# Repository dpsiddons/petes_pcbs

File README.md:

# petes_pcbs
various PCB designs

THis is a collection of small PCB designs (in KiCad) that I have done, some for my research adn some for my hobbies. This is just a place to keep them where they are accessible to myself and my colleagues.

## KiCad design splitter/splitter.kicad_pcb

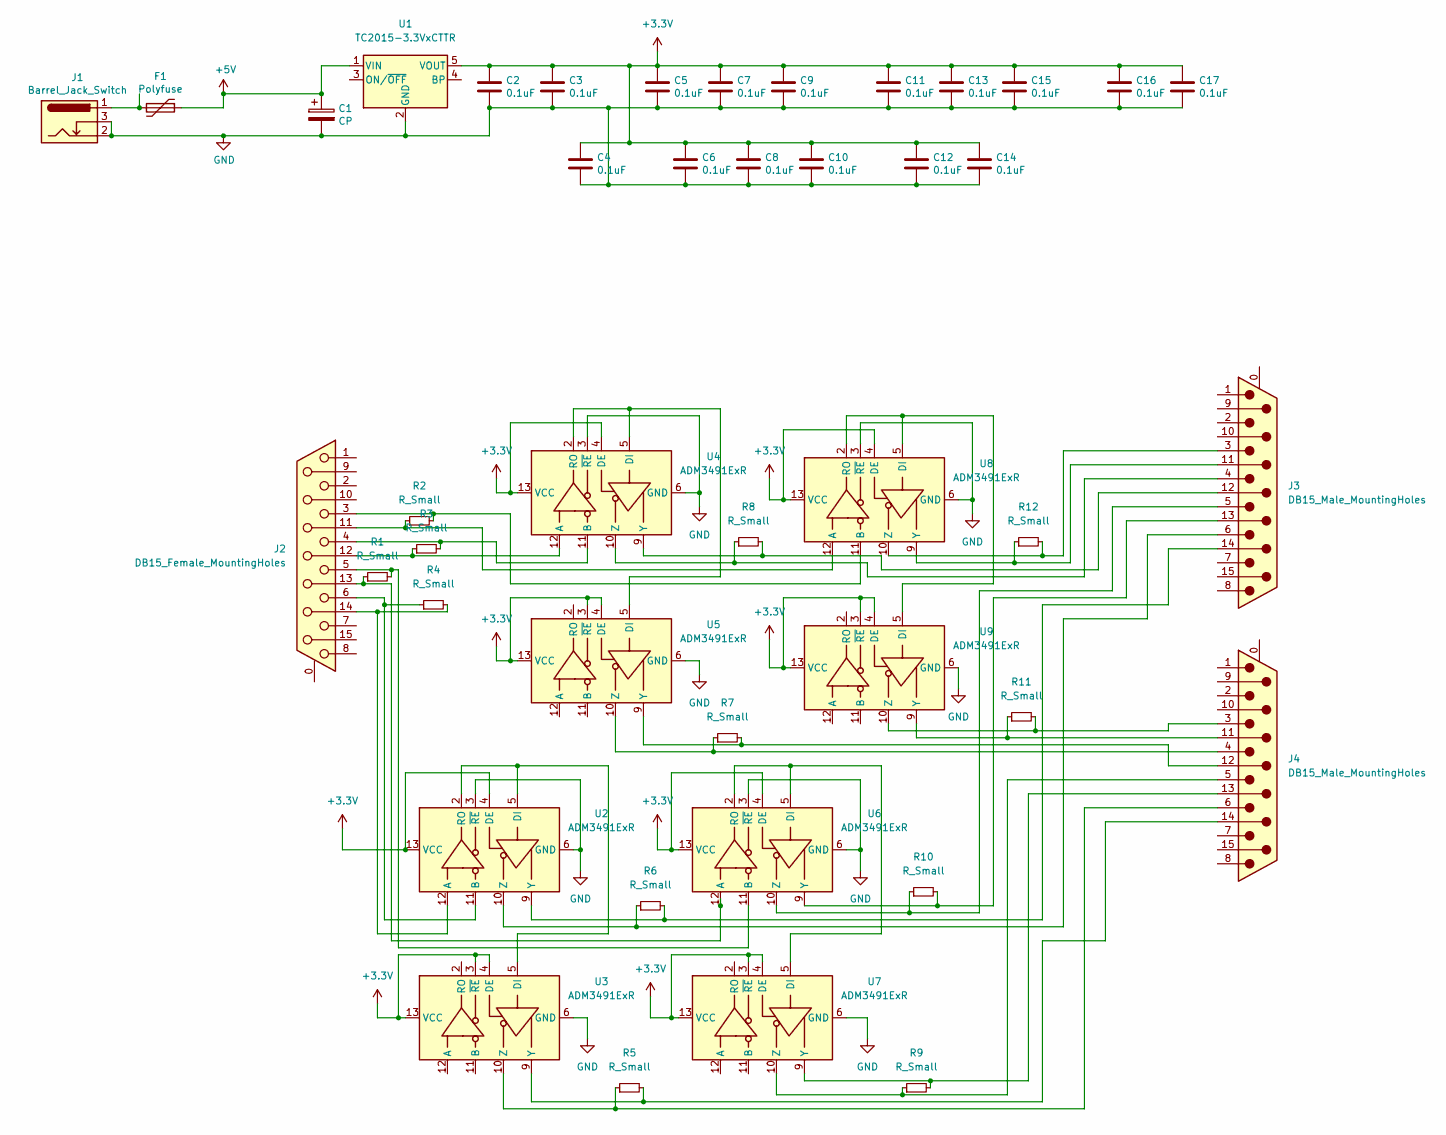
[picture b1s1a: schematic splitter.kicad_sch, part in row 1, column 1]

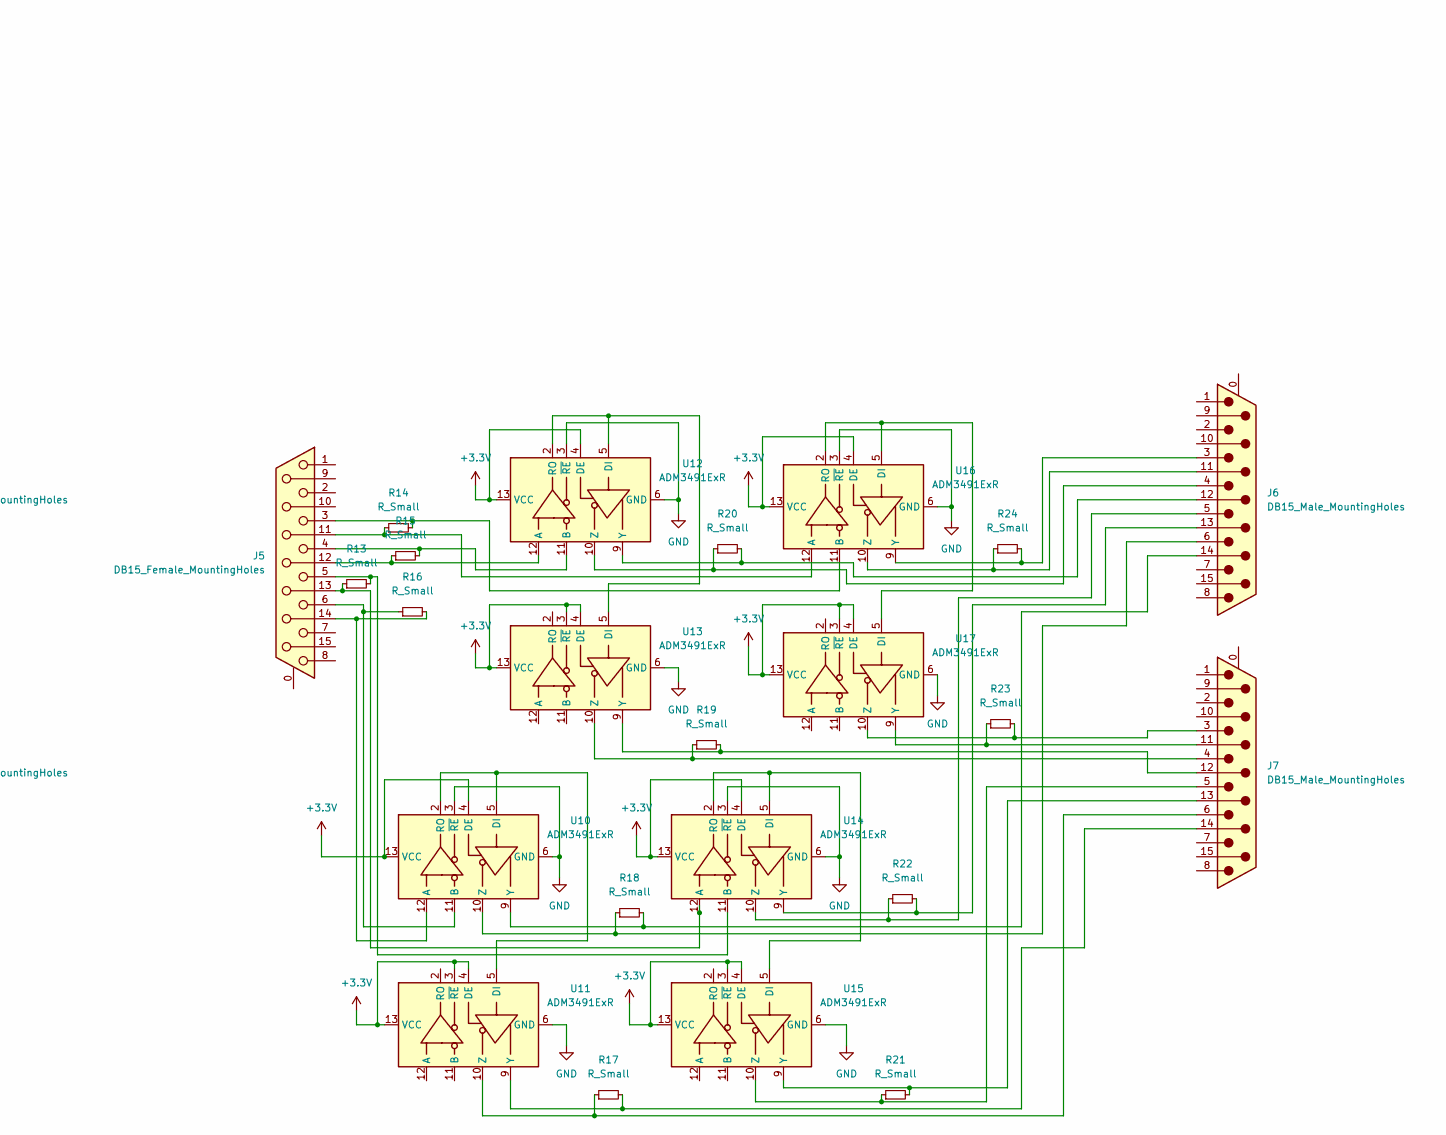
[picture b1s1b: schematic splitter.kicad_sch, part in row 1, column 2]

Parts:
C1: CP; CP_Elec_5x3
C2, C3, C4, C5, C6, C7, C8, C9, C10, C11, C12, C13, C14, C15, C16, C17: 0.1uF; C_0805_2012Metric
F1: Polyfuse; Fuse_2920_7451Metric
J1: Barrel_Jack_Switch; BarrelJack_GCT_DCJ200-10-A_Horizontal
J2, J5: DB15_Female_MountingHoles; DSUB-15_Female_Horizontal_P2.77x2.84mm_EdgePinOffset4.94mm_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
J3, J4, J6, J7: DB15_Male_MountingHoles; DSUB-15_Male_Horizontal_P2.77x2.84mm_EdgePinOffset4.94mm_Ho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
R1, R2, R3, R4, R5, R6, R7, R8, R9, R10, R11, R12, R13, R14, R15, R16, R17, R18, R19, R20, R21, R22, R23, R24: R_Small; R_0402_1005Metric_Pad0.72x0.64mm_HandSolder
U1: TC2015-3.3VxCTTR; SOT-23-5
U2, U3, U4, U5, U6, U7, U8, U9, U10, U11, U12, U13, U14, U15, U16, U17: ADM3491ExR; SOIC-14_3.9x8.7mm_P1.27mm

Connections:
+3V3: C2.1, C3.1, C4.1, C5.1, C6.1, C7.1, C8.1, C9.1, C10.1, C11.1, C12.1, C13.1, C14.1, C15.1, C16.1, C17.1, U1.5 (VOUT), U2.4 (DE), U2.13 (VCC), U2.14 (VCC), U3.3 (~RE), U3.4 (DE), U3.13 (VCC), U3.14 (VCC), U4.4 (DE), U4.13 (VCC), U4.14 (VCC), U5.3 (~RE), U5.4 (DE), U5.13 (VCC), U5.14 (VCC), U6.4 (DE), U6.13 (VCC), U6.14 (VCC), U7.3 (~RE), U7.4 (DE), U7.13 (VCC), U7.14 (VCC), U8.4 (DE), U8.13 (VCC), U8.14 (VCC), U9.3 (~RE), U9.4 (DE), U9.13 (VCC), U9.14 (VCC), U10.4 (DE), U10.13 (VCC), U10.14 (VCC), U11.3 (~RE), U11.4 (DE), U11.13 (VCC), U11.14 (VCC), U12.4 (DE), U12.13 (VCC), U12.14 (VCC), U13.3 (~RE), U13.4 (DE), U13.13 (VCC), U13.14 (VCC), U14.4 (DE), U14.13 (VCC), U14.14 (VCC), U15.3 (~RE), U15.4 (DE), U15.13 (VCC), U15.14 (VCC), U16.4 (DE), U16.13 (VCC), U16.14 (VCC), U17.3 (~RE), U17.4 (DE), U17.13 (VCC), U17.14 (VCC)
+5V: C1.1, F1.1, U1.1 (VIN)
GND: C1.2, C2.2, C3.2, C4.2, C5.2, C6.2, C7.2, C8.2, C9.2, C10.2, C11.2, C12.2, C13.2, C14.2, C15.2, C16.2, C17.2, J1.2, J1.3, U1.2 (GND), U2.3 (~RE), U2.6 (GND), U2.7 (GND), U3.6 (GND), U3.7 (GND), U4.3 (~RE), U4.6 (GND), U4.7 (GND), U5.6 (GND), U5.7 (GND), U6.3 (~RE), U6.6 (GND), U6.7 (GND), U7.6 (GND), U7.7 (GND), U8.3 (~RE), U8.6 (GND), U8.7 (GND), U9.6 (GND), U9.7 (GND), U10.3 (~RE), U10.6 (GND), U10.7 (GND), U11.6 (GND), U11.7 (GND), U12.3 (~RE), U12.6 (GND), U12.7 (GND), U13.6 (GND), U13.7 (GND), U14.3 (~RE), U14.6 (GND), U14.7 (GND), U15.6 (GND), U15.7 (GND), U16.3 (~RE), U16.6 (GND), U16.7 (GND), U17.6 (GND), U17.7 (GND)
unnamed: F1.2, J1.1
unnamed: J2.3, R2.2, U8.11 (B)
unnamed: J2.4, R3.2, U4.11 (B)
unnamed: J2.5, R1.2, U6.11 (B)
unnamed: J2.6, R4.1, U2.11 (B)
unnamed: J2.11 (P111), R2.1, U8.12 (A)
unnamed: J2.12, R3.1, U4.12 (A)
unnamed: J2.13, R1.1, U6.12 (A)
unnamed: J2.14, R4.2, U2.12 (A)
unnamed: J3.3, R12.2, U8.10 (Z)
unnamed: J3.4, R8.1, U4.10 (Z)
unnamed: J3.5, R10.1, U6.10 (Z)
unnamed: J3.6, R6.1, U2.10 (Z)
unnamed: J3.11 (P111), R12.1, U8.9 (Y)
unnamed: J3.12, R8.2, U4.9 (Y)
unnamed: J3.13, R10.2, U6.9 (Y)
unnamed: J3.14, R6.2, U2.9 (Y)
unnamed: J4.3, R11.2, U9.10 (Z)
unnamed: J4.4, R7.1, U5.10 (Z)
unnamed: J4.5, R9.1, U7.10 (Z)
unnamed: J4.6, R5.1, U3.10 (Z)
unnamed: J4.11 (P111), R11.1, U9.9 (Y)
unnamed: J4.12, R7.2, U5.9 (Y)
unnamed: J4.13, R9.2, U7.9 (Y)
unnamed: J4.14, R5.2, U3.9 (Y)
unnamed: J5.3, R14.2, U16.11 (B)
unnamed: J5.4, R15.2, U12.11 (B)
unnamed: J5.5, R13.2, U14.11 (B)
unnamed: J5.6, R16.1, U10.11 (B)
unnamed: J5.11 (P111), R14.1, U16.12 (A)
unnamed: J5.12, R15.1, U12.12 (A)
unnamed: J5.13, R13.1, U14.12 (A)
unnamed: J5.14, R16.2, U10.12 (A)
unnamed: J6.3, R24.2, U16.9 (Y)
unnamed: J6.4, R20.1, U12.10 (Z)
unnamed: J6.5, R22.1, U14.10 (Z)
unnamed: J6.6, R18.1, U10.10 (Z)
unnamed: J6.12, R20.2, U12.9 (Y)
unnamed: J6.13, R22.2, U14.9 (Y)
unnamed: J6.14, R18.2, U10.9 (Y)
unnamed: J7.3, R23.2, U17.10 (Z)
unnamed: J7.4, R19.1, U13.10 (Z)
unnamed: J7.5, R21.1, U15.10 (Z)
unnamed: J7.6, R17.1, U11.10 (Z)
unnamed: J7.11 (P111), R23.1, U17.9 (Y)
unnamed: J7.12, R19.2, U13.9 (Y)
unnamed: J7.13, R21.2, U15.9 (Y)
unnamed: J7.14, R17.2, U11.9 (Y)
unnamed: U2.2 (RO), U2.5 (DI), U3.5 (DI)
unnamed: U4.2 (RO), U4.5 (DI), U5.5 (DI)
unnamed: U6.2 (RO), U6.5 (DI), U7.5 (DI)
unnamed: U8.2 (RO), U8.5 (DI), U9.5 (DI)
unnamed: U10.2 (RO), U10.5 (DI), U11.5 (DI)
unnamed: U12.2 (RO), U12.5 (DI), U13.5 (DI)
unnamed: U14.2 (RO), U14.5 (DI), U15.5 (DI)
unnamed: U16.2 (RO), U16.5 (DI), U17.5 (DI)
unnamed: J6.11 (P111), R24.1, U16.10 (Z)

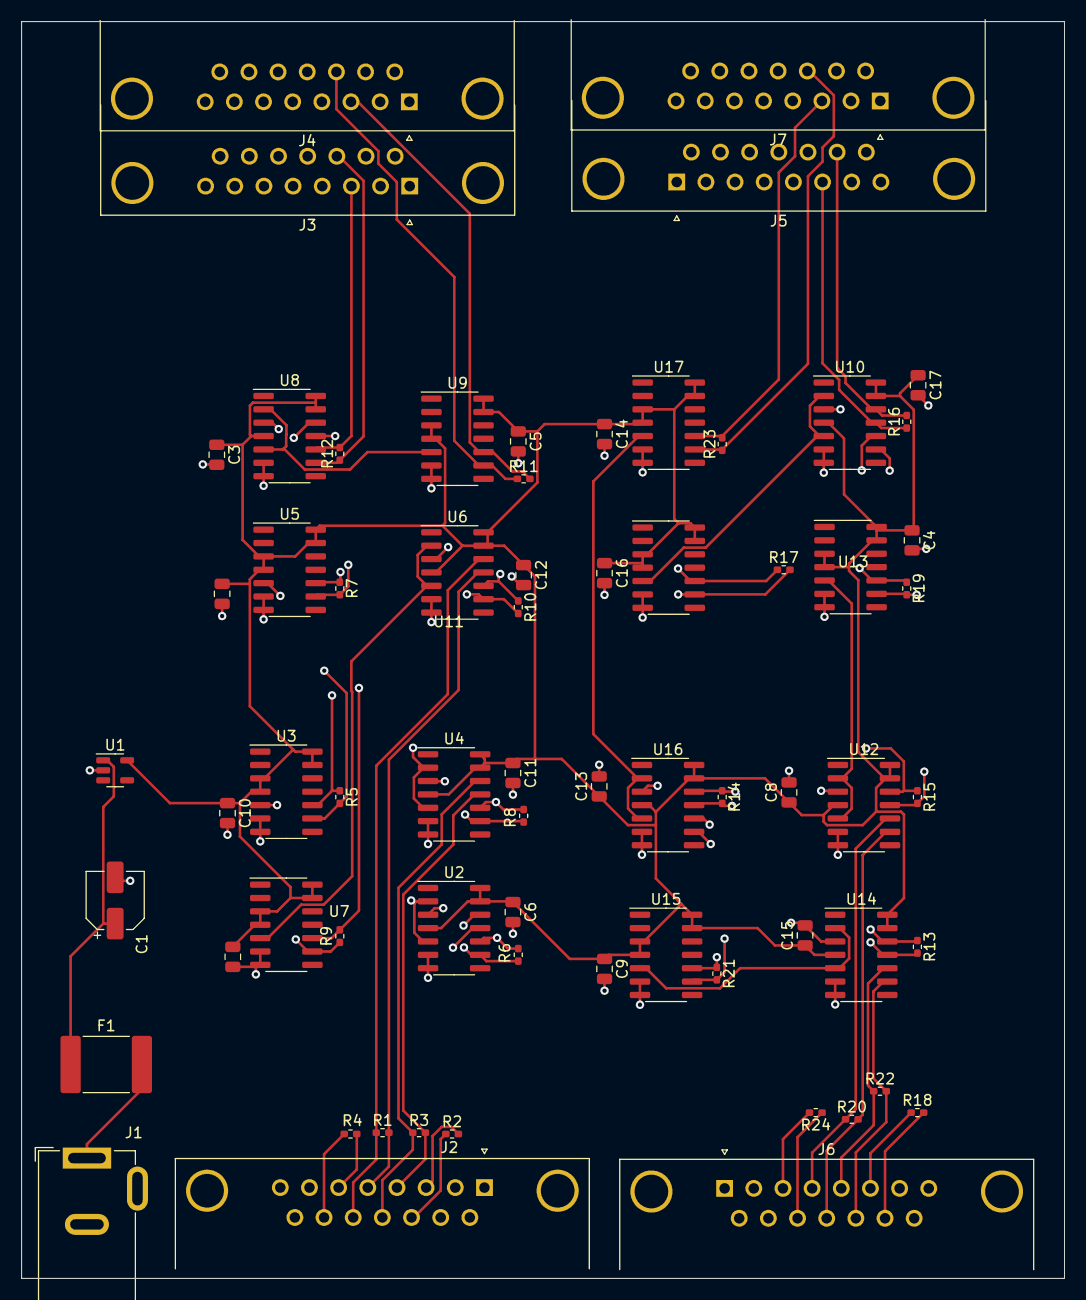
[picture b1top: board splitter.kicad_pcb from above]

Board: 4 copper layers, 99.1 x 119.4 mm, 66 parts (0 on the bottom side), 60 nets.

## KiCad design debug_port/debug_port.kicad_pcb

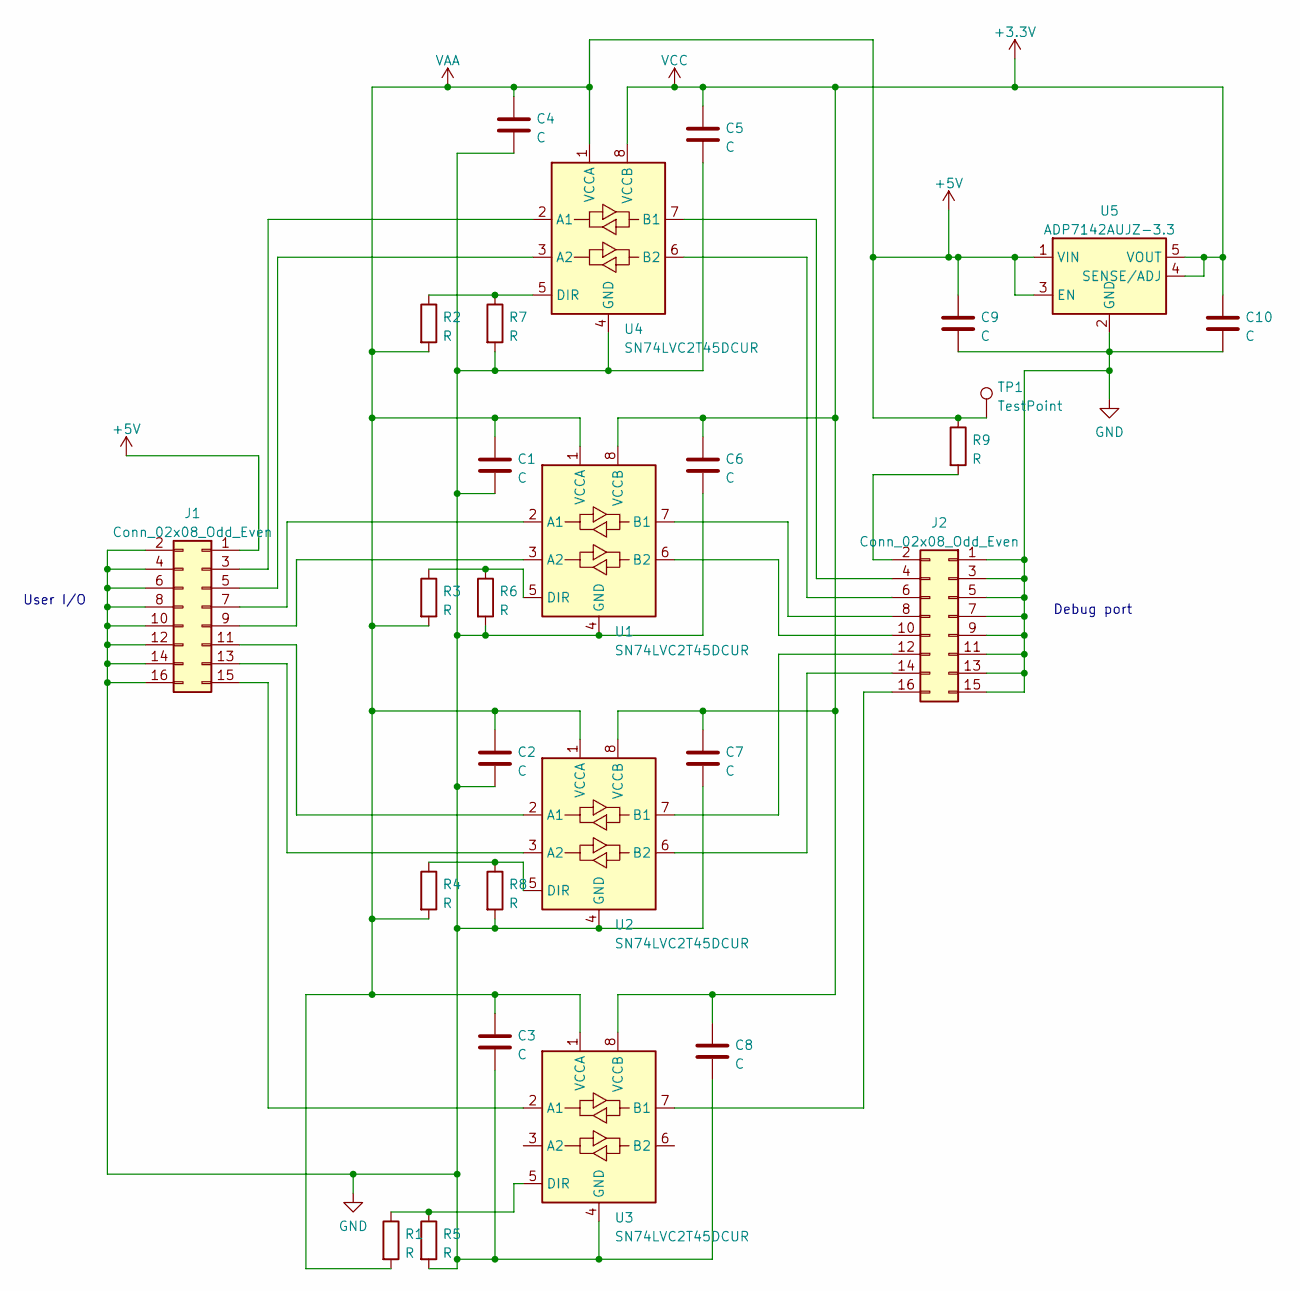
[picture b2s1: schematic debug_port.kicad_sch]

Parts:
C1, C2, C3, C4, C5, C6, C7, C8, C9, C10: C; C_0603_1608Metric_Pad1.08x0.95mm_HandSolder
J1: Conn_02x08_Odd_Even; PinHeader_2x08_P2.54mm_Vertical
J2: Conn_02x08_Odd_Even; PinSocket_2x08_P2.54mm_Horizontal
R1, R2, R3, R4, R5, R6, R7, R8, R9: R; R_0402_1005Metric_Pad0.72x0.64mm_HandSolder
TP1: TestPoint; TestPoint_Pad_1.0x1.0mm
U1, U2, U3, U4: SN74LVC2T45DCUR; VSSOP-8_2.4x2.1mm_P0.5mm
U5: ADP7142AUJZ-3.3; TSOT-23-5

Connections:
+3.3V: C5.1, C6.1, C7.1, C8.1, C10.1, U1.8 (VCCB), U2.8 (VCCB), U3.8 (VCCB), U4.8 (VCCB), U5.4 (SENSE/ADJ), U5.5 (VOUT)
+5V: C1.1, C2.1, C3.1, C4.1, C9.1, J1.1, R1.2, R2.2, R3.2, R4.2, R9.1, TP1.1, U1.1 (VCCA), U2.1 (VCCA), U3.1 (VCCA), U4.1 (VCCA), U5.1 (VIN), U5.3 (EN)
GND: C1.2, C2.2, C3.2, C4.2, C5.2, C6.2, C7.2, C8.2, C9.2, C10.2, J1.2, J1.4, J1.6, J1.8, J1.10, J1.12, J1.14, J1.16, J2.1, J2.3, J2.5, J2.7, J2.9, J2.11, J2.13, J2.15, R5.2, R6.2, R7.2, R8.2, U1.4 (GND), U2.4 (GND), U3.4 (GND), U4.4 (GND), U5.2 (GND)
unnamed: J1.3, U4.2 (A1)
unnamed: J1.5, U4.3 (A2)
unnamed: J1.7, U1.2 (A1)
unnamed: J1.9, U1.3 (A2)
unnamed: J1.15, U3.2 (A1)
unnamed: J2.2, R9.2
unnamed: J2.4, U4.7 (B1)
unnamed: J2.6, U4.6 (B2)
unnamed: J2.8, U1.7 (B1)
unnamed: J2.10, U1.6 (B2)
unnamed: J2.12, U2.7 (B1)
unnamed: J2.14, U2.6 (B2)
unnamed: J2.16, U3.7 (B1)
unnamed: R1.1, R5.1, U3.5 (DIR)
unnamed: R2.1, R7.1, U4.5 (DIR)
unnamed: R3.1, R6.1, U1.5 (DIR)
unnamed: R4.1, R8.1, U2.5 (DIR)
unnamed: J1.11, U2.2 (A1)
unnamed: J1.13, U2.3 (A2)

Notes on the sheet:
User I/O
Debug port

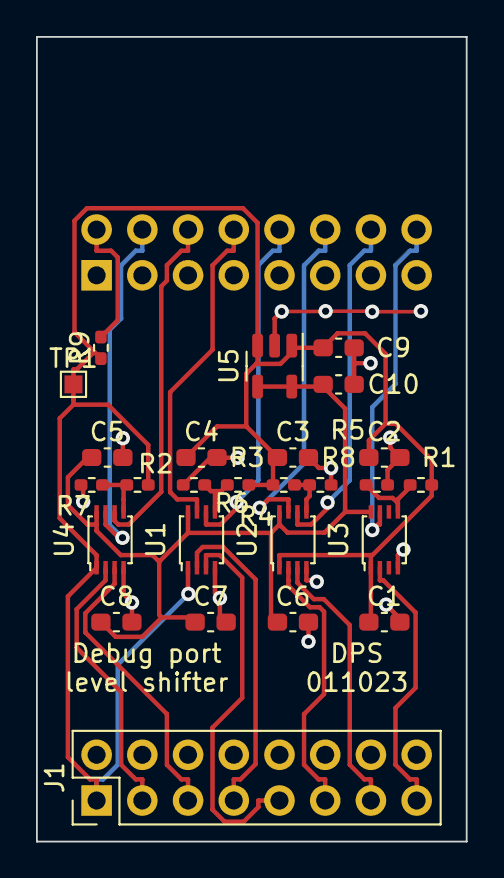
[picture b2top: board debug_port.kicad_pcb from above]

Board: 2 copper layers, 23.9 x 44.7 mm, 27 parts (1 on the bottom side), 22 nets.
